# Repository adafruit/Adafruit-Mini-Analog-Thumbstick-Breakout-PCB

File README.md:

## Adafruit Mini Analog Thumbstick Breakout PCB
<a href="http://www.adafruit.com/products/3246"><br/>
Click here to purchase one from the Adafruit shop</a>

Are you itching for an easy way to mount a PSP-like thumb joystick to your project? This Analog Mini Thumbstick Breakout Board will help you do just that!

This is a neat little PCB, on which you can mount a joystick/thumbstick -- we recommend this one. Since it's analog, you'll need two analog reading pins on your microcontroller to determine X and Y.

We designed the breakout so that you can attach the thumbstick to a panel easily. A 4-pin 0.1" spaced header makes it easy to connect either in a perfboard/breadboard setting or free wiring, with header on both siders it is mechanically stable. You'll need to solder a thumbstick into the PCB using a soldering iron and solder, but its very simple and will only take a minute.

Includes 1 x 8-pin 0.1 inch male header. Note: Thumbstick itself is not included.

PCB files for the Adafruit Mini Analog Thumbstick Breakout. The format is EagleCAD schematic and board layout
- http://www.adafruit.com/products/3246

### License

Adafruit invests time and resources providing this open source design, please support Adafruit and open-source hardware by purchasing products from [Adafruit](https://www.adafruit.com)!

All text above must be included in any redistribution

Designed by Limor Fried/Ladyada for Adafruit Industries.
Creative Commons Attribution/Share-Alike, all text above must be included in any redistribution. 
See license.txt for additional information.

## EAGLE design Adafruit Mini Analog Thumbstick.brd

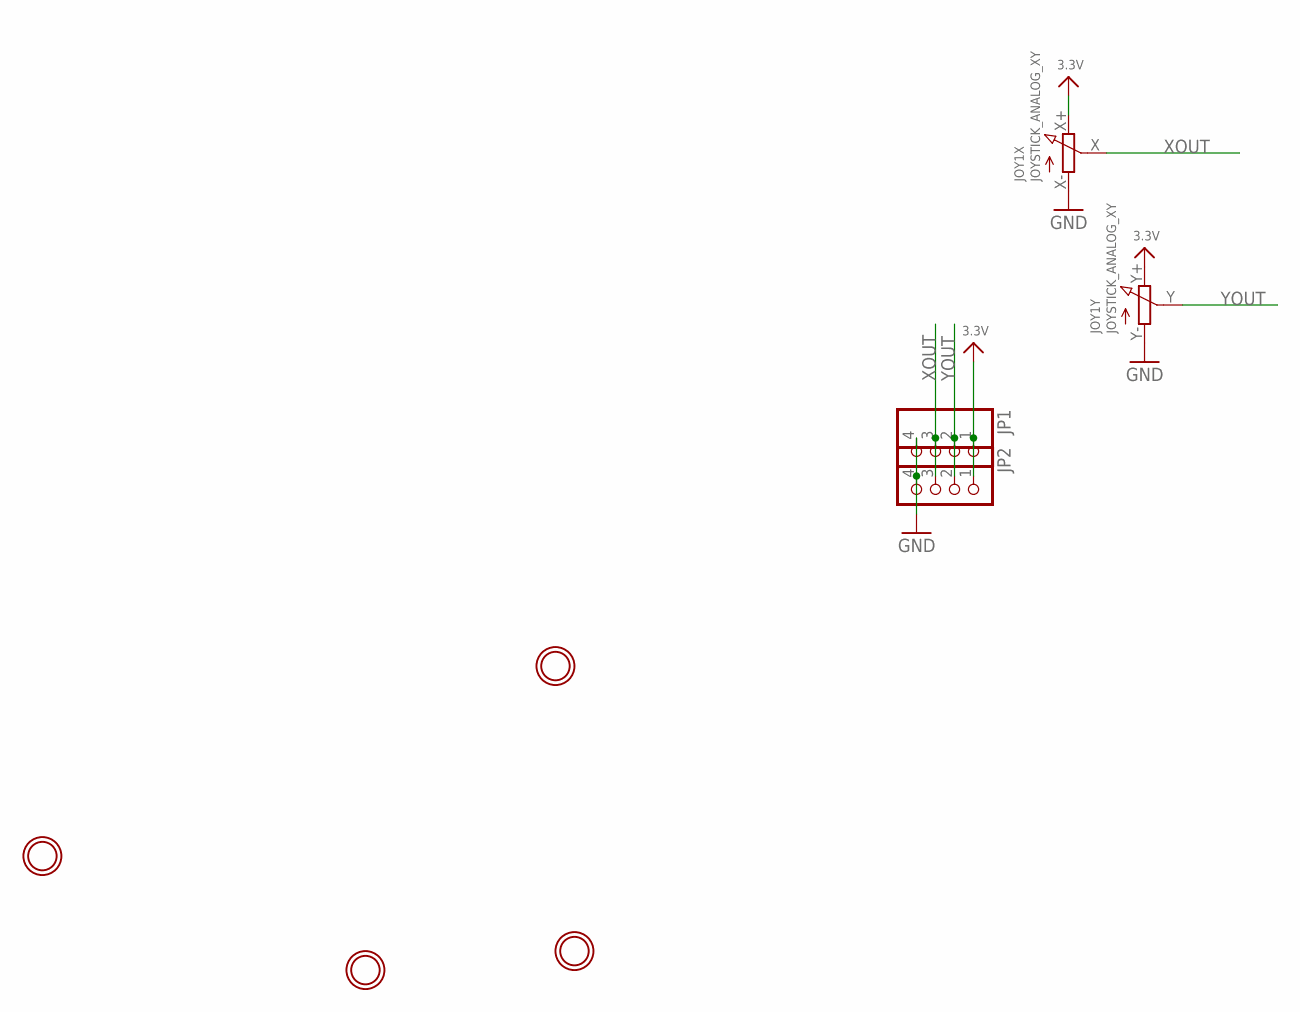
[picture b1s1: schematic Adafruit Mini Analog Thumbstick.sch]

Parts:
JOY1: JOYSTICK_ANALOG_XY; JOYSTICK_ANALOG_MINITHM
JP1, JP2: HEADER-1X476MIL; 1X04_ROUND_76
U$1, U$4, U$5, U$6: MOUNTINGHOLE2.0; MOUNTINGHOLE_2.0_PLATED

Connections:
3.3V: JOY1.X+ (E), JOY1.Y+ (E), JP1.1, JP2.1
GND: JOY1.X- (A), JOY1.Y- (A), JP1.4, JP2.4
XOUT: JOY1.X (S), JP1.3, JP2.3
YOUT: JOY1.Y (S), JP1.2, JP2.2

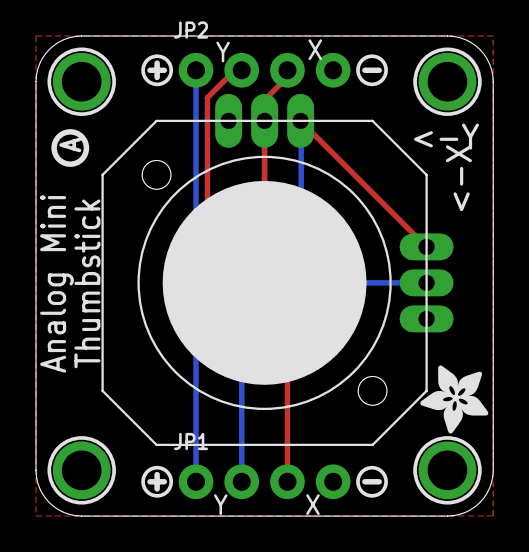
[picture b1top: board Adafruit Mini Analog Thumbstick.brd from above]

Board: 2 copper layers, 25.4 x 26.7 mm, 13 parts (0 on the bottom side), 4 nets.

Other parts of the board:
U$8: ADAFRUIT_3.5MM
U$9, U$10: SYMBOL_PLUS
U$11, U$12: SYMBOL_MINUS
U$13: PCBFEAT-REV-040

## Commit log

2016-08-30 init
2016-08-30 fix url
2016-08-30 neaten schem
2016-08-30 typo auth

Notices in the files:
parts and their libraries:
microbuilder: This work is placed in the public domain, and may be freely used for commercial and non-commercial work with the following conditions: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
